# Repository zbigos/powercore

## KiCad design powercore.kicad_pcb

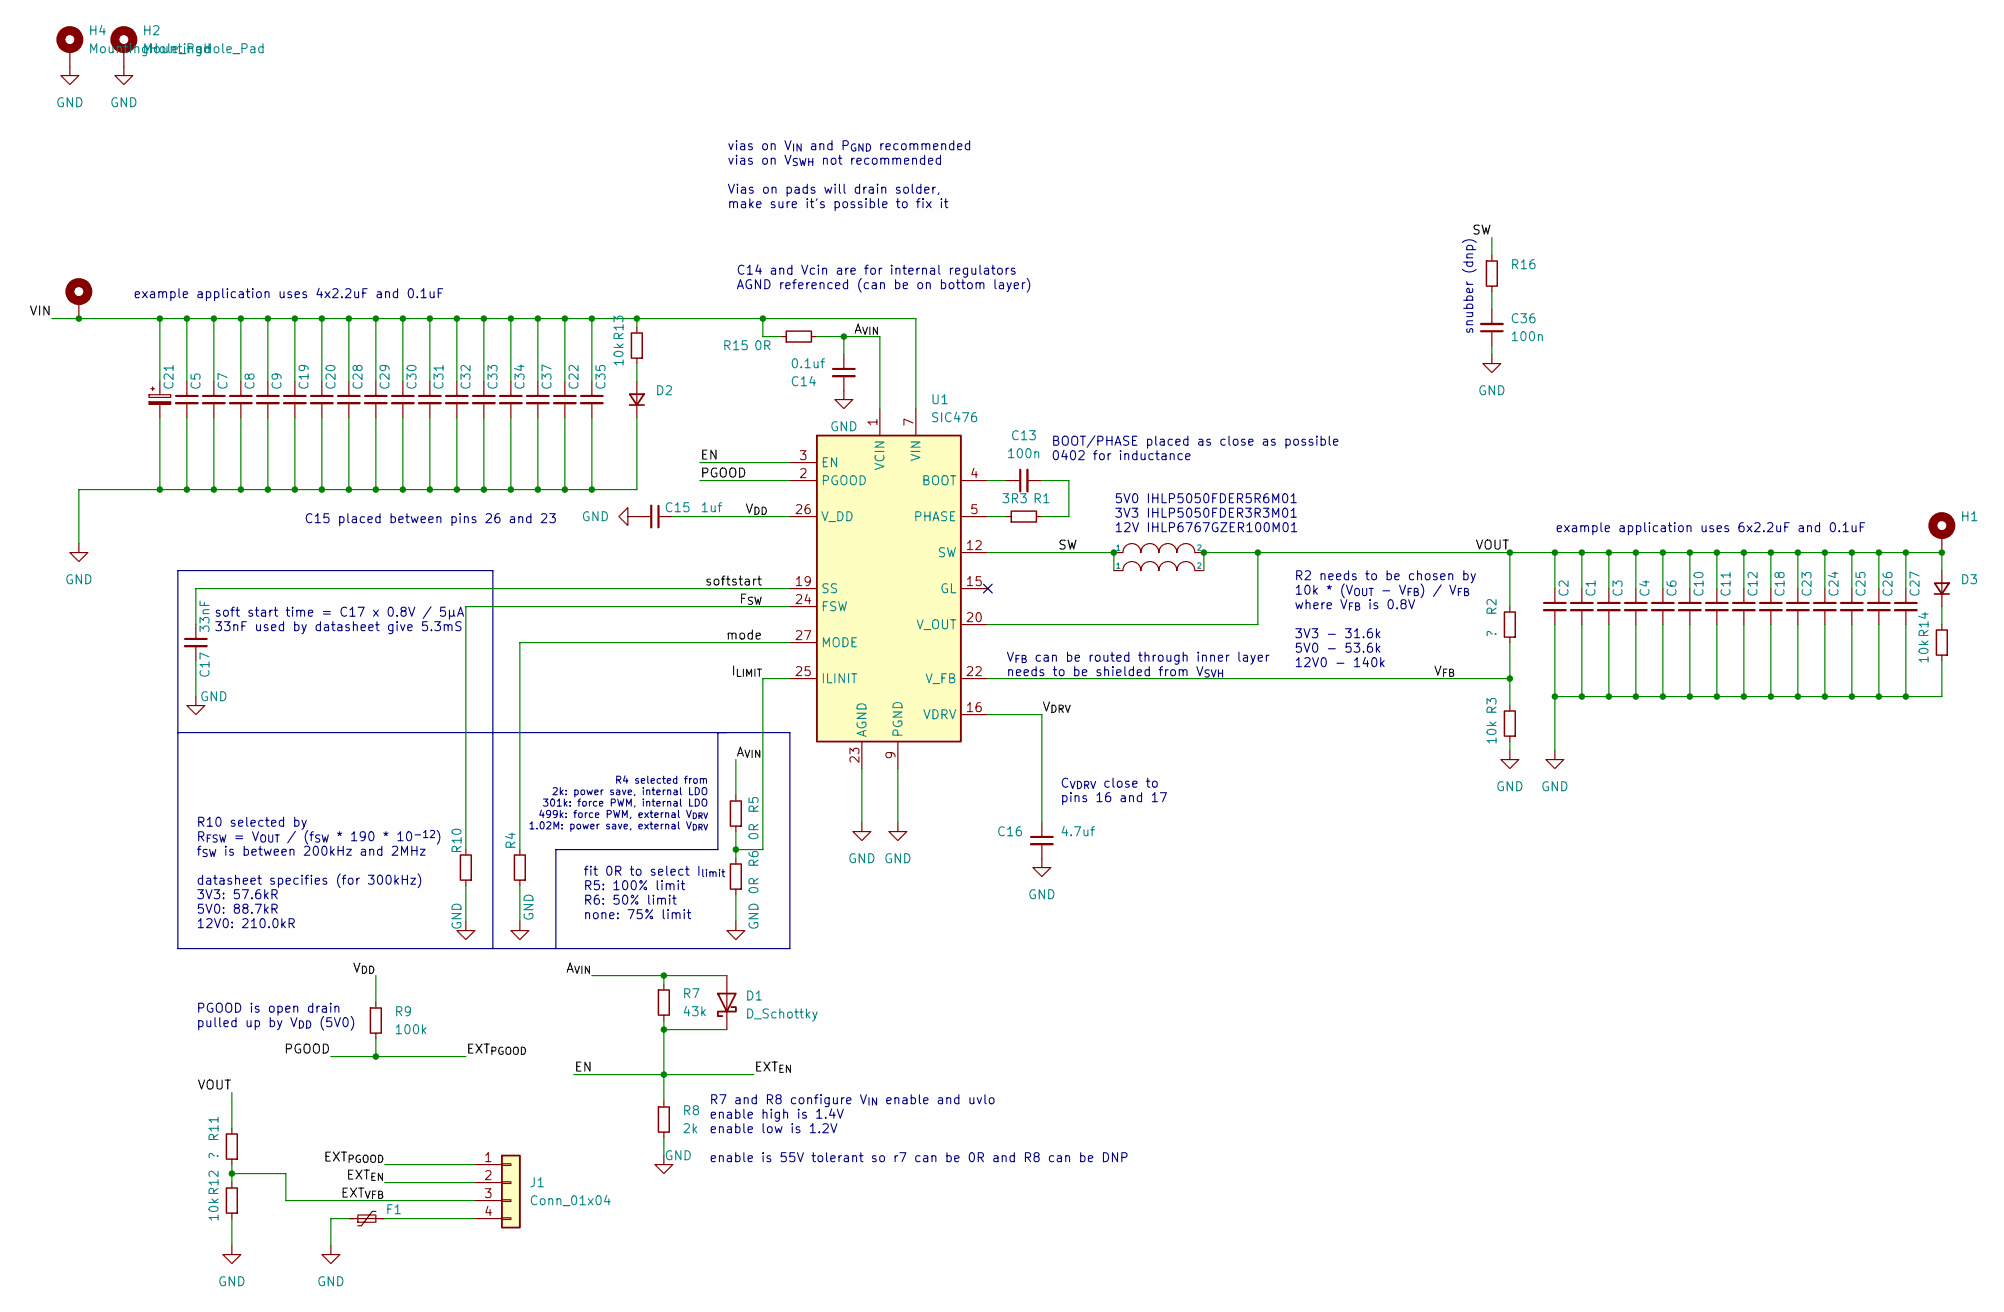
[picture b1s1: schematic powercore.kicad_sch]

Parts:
C1, C2, C3, C4, C5, C6, C7, C8, C9, C10, C11, C12, C18, C20, C28, C29: C_Small; C_1206_3216Metric
C13: 100n; C_0402_1005Metric
C14: 0.1uf; C_0603_1608Metric
C15: 1uf; C_0805_2012Metric
C16: 4.7uf; C_0603_1608Metric
C17: 33nF; C_0603_1608Metric
C19, C22, C35, C37: C_Small; C_0603_1608Metric
C21: C_Polarized_Small; CP_Elec_8x10
C23, C24, C25, C26, C27, C30, C31, C32, C33, C34: C_Small; C_1210_3225Metric
C36: 100n; C_0603_1608Metric
D1: D_Schottky; D_SOD-323
D2, D3: D_Small; D_0805_2012Metric
F1: Polyfuse_Small; Fuse_0603_1608Metric
H1, H2, H3, H4: MountingHole_Pad; MountingHole_2.2mm_M2_Pad_Via
J1: Conn_01x04; JST_GH_SM04B-GHS-TB_1x04-1MP_P1.25mm_Horizontal
L1: INDUCTOR; L_Vishay_IHLP-6767
L2: INDUCTOR; L_Vishay_IHLP-5050
R1: 3R3; R_0402_1005Metric
R2, R4, R10, R11: ?; R_0603_1608Metric
R3, R12, R13, R14: 10k; R_0603_1608Metric
R5, R6, R15: 0R; R_0603_1608Metric
R7: 43k; R_0603_1608Metric
R8: 2k; R_0603_1608Metric
R9: 100k; R_0603_1608Metric
R16: R_Small; R_0603_1608Metric
U1: SIC476; Vishay_PowerPAK_MLP55-27L

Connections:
/A_{VIN}: C14.1, D1.2 (A), R5.2, R7.1, R15.2, U1.1 (VCIN)
/EN: D1.1 (K), J1.2, R7.2, R8.1, U1.3 (EN)
/EXT_{PGOOD}: J1.1, R9.2, U1.2 (PGOOD)
/EXT_{VFB}: J1.3, R11.1, R12.2
/F_{SW}: R10.2, U1.24 (FSW)
/I_{LIMIT}: R5.1, R6.2, U1.25 (ILINIT)
/SW: L1.1, L2.1, R16.1, U1.12 (SW), U1.13 (SW), U1.14 (SW)
/VIN: C5.1, C7.1, C8.1, C9.1, C19.1, C20.1, C21.1, C22.1, C28.1, C29.1, C30.1, C31.1, C32.1, C33.1, C34.1, C35.1, C37.1, H3.1, R13.2, R15.1, U1.7 (VIN), U1.8 (VIN), U1.29 (VIN)
/VOUT: C1.1, C2.1, C3.1, C4.1, C6.1, C10.1, C11.1, C12.1, C18.1, C23.1, C24.1, C25.1, C26.1, C27.1, D3.2 (A), H1.1, L1.2, L2.2, R2.2, R11.2, U1.20 (V_OUT)
/V_{DD}: C15.1, R9.1, U1.26 (V_DD)
/V_{DRV}: C16.1, U1.16 (VDRV)
/V_{FB}: R2.1, R3.2, U1.22 (V_FB)
/mode: R4.2, U1.27 (MODE)
/softstart: C17.1, U1.19 (SS)
GND: C1.2, C2.2, C3.2, C4.2, C5.2, C6.2, C7.2, C8.2, C9.2, C10.2, C11.2, C12.2, C14.2, C15.2, C16.2, C17.2, C18.2, C19.2, C20.2, C21.2, C22.2, C23.2, C24.2, C25.2, C26.2, C27.2, C28.2, C29.2, C30.2, C31.2, C32.2, C33.2, C34.2, C35.2, C36.1, C37.2, D2.1 (K), F1.1, H2.1, H4.1, R3.1, R4.1, R6.1, R8.2, R10.1, R12.1, R14.1, U1.9 (PGND), U1.10 (PGND), U1.11 (PGND), U1.17 (PGND), U1.23 (AGND), U1.28 (AGND), U1.30 (PGND)
unnamed: C13.1, U1.4 (BOOT)
unnamed: C13.2, R1.2
unnamed: C36.2, R16.2
unnamed: D2.2 (A), R13.1
unnamed: D3.1 (K), R14.2
unnamed: F1.2, J1.4
unnamed: R1.1, U1.5 (PHASE), U1.6 (PHASE)

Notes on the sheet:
R4 selected from 2k: power save, internal LDO 301k: force PWM, internal LDO 499k: force PWM, external V_{DRV} 1.02M: power save, external V_{DRV}
C_{VDRV} close to pins 16 and 17
C14 and Vcin are for internal regulators AGND referenced (can be on bottom layer)
vias on V_{IN} and P_{GND} recommended vias on V_{SWH} not recommended Vias on pads will drain solder, make sure it's possible to fix it
example application uses 6x2.2uF and 0.1uF
5V0 IHLP5050FDER5R6M01 3V3 IHLP5050FDER3R3M01 12V IHLP6767GZER100M01
PGOOD is open drain pulled up by V_{DD} (5V0)
soft start time = C17 x 0.8V / 5μA 33nF used by datasheet give 5.3mS
R7 and R8 configure V_{IN} enable and uvlo enable high is 1.4V enable low is 1.2V enable is 55V tolerant so r7 can be 0R and R8 can be DNP
C15 placed between pins 26 and 23
fit 0R to select I_{limit} R5: 100% limit R6: 50% limit none: 75% limit
R2 needs to be chosen by 10k * (V_{OUT} - V_{FB}) / V_{FB} where V_{FB} is 0.8V 3V3 - 31.6k 5V0 - 53.6k 12V0 - 140k
V_{FB} can be routed through inner layer needs to be shielded from V_{SVH}
snubber (dnp)
example application uses 4x2.2uF and 0.1uF
BOOT/PHASE placed as close as possible 0402 for inductance
R10 selected by R_{FSW} = V_{OUT} / (f_{SW} * 190 * 10^{-12}) f_{SW} is between 200kHz and 2MHz datasheet specifies (for 300kHz) 3V3: 57.6kR 5V0: 88.7kR 12V0: 210.0kR

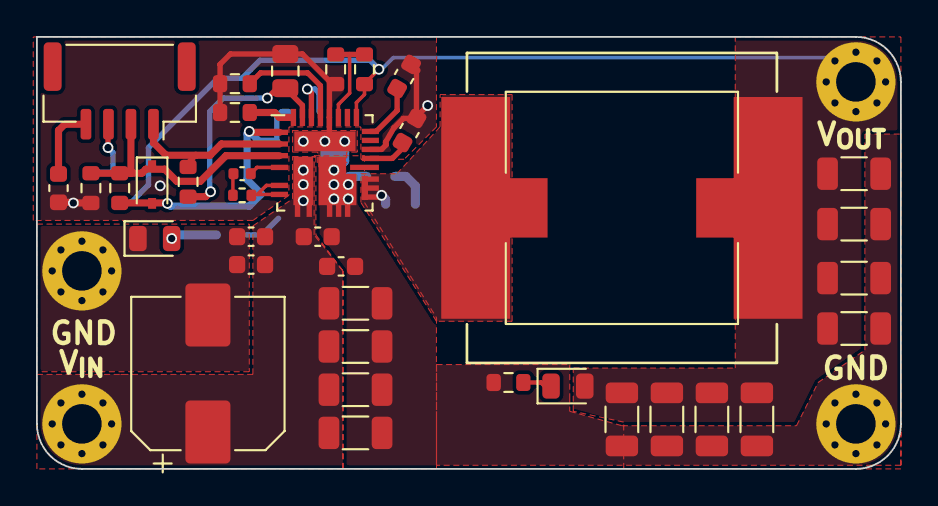
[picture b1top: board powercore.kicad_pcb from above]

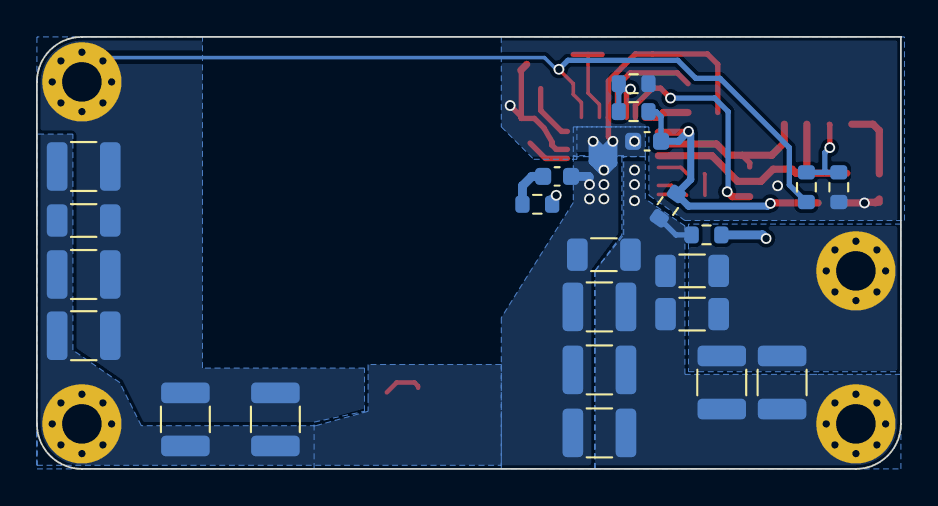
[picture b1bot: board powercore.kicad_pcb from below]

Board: 4 copper layers, 48.0 x 24.0 mm, 65 parts (23 on the bottom side), 22 nets.

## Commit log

2022-05-29 initial
